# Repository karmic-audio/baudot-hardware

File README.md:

# baudot hardware

Based on the Monome Teletype.

Schematic/PCB diagram converted from Eagle to KiCAD.

Firmware: https://github.com/karmic-audio/baudot-software

## License

CC-BY-SA 3.0. Do not use the name "monome" or "teletype" in derivative works.

Created by brian crabtree (bcrabtree@monome.org)
Modified by Serge Bazanski (q3k@q3k.org) for Karmic Audio.

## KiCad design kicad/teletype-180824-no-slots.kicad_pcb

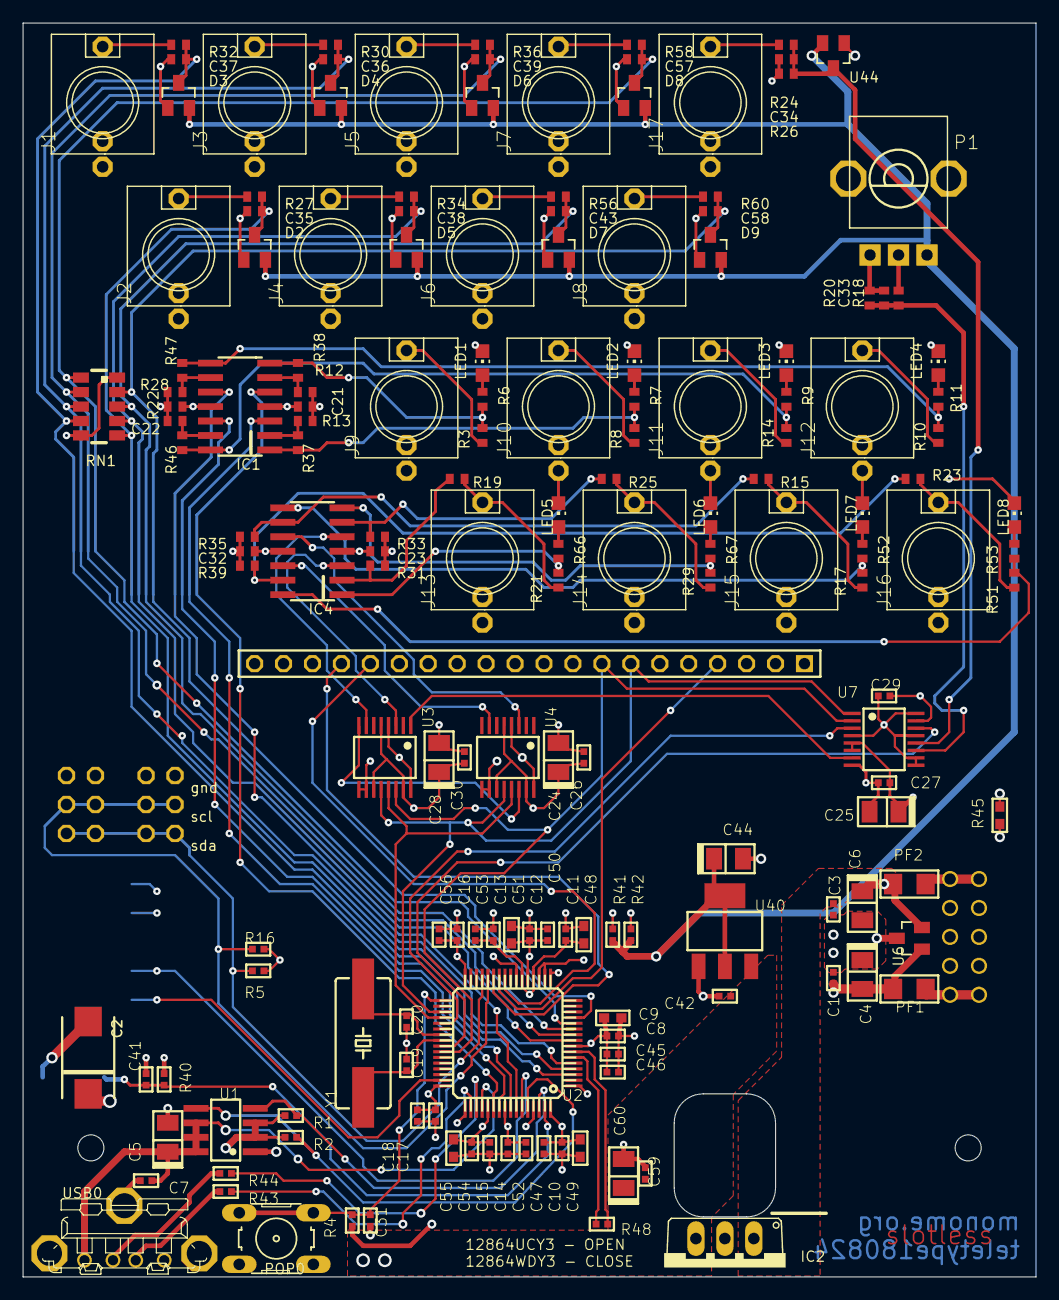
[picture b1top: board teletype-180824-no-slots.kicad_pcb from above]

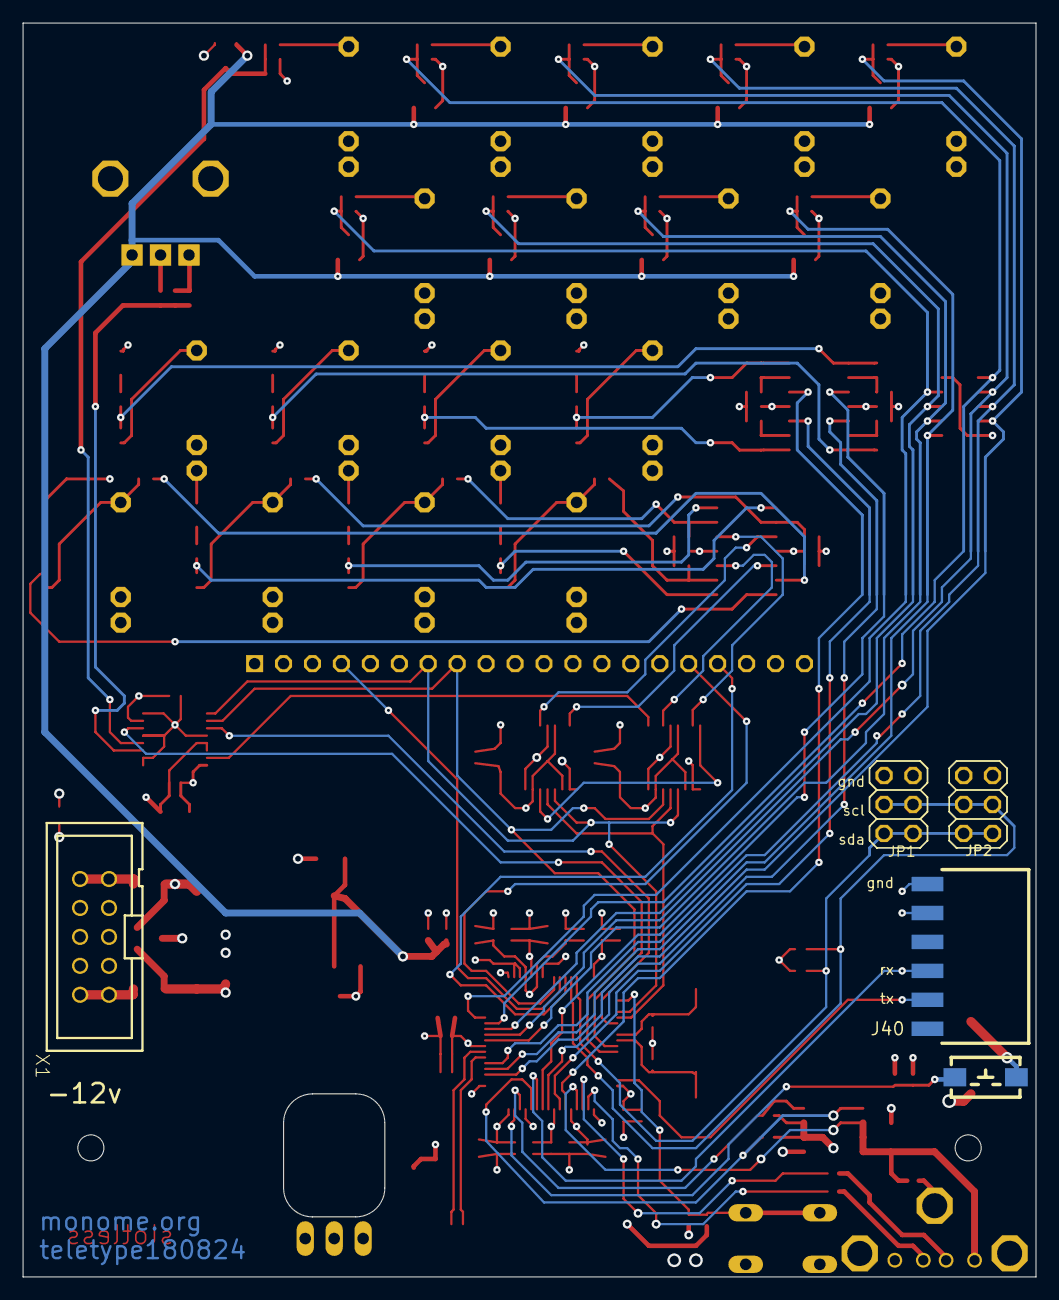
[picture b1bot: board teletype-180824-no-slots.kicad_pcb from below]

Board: 4 copper layers, 88.9 x 110.0 mm, 172 parts (5 on the bottom side), 98 nets.

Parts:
C1, C3, C7, C18, C21, C22, C23, C26, C27, C29, C30, C31, C32, C41, C42, C46, C47, C50, C56, C59: 100n; C0402
C2: 220u; C7343-43
C4, C6, C24, C25, C28, C44, C60: 10u; C1206_T
C5: 4.7u; C1206_T
C8, C13, C14, C15: 2.7n; C0402
C9, C48, C55: 2.2u; C0603
C10, C12, C16, C17, C33, C45, C52, C53, C54: 33n; C0402
C11: 470p; C0402
C19, C20: 22p; C0402
C34, C35, C36, C37, C38, C39, C43, C57, C58: 1n; C0402
C49, C51: 4.7u; C0603
D2, D3, D4, D5, D6, D7, D8, D9: BAS70-04; SOT23
IC1: TL074; SO14
IC2: OKI-78SR; TO220V
IC4: OPA4171; SO14
J1, J2, J3, J4, J5, J6, J7, J8, J9, J10, J11, J12, J13, J14, J15, J16, J17: WQP-PJ301M-12_JACK
J40: ISP-ROW
JP1, JP2: 2X03
JP5: OLED128X64; OLED-ALEPH
LED1, LED2, LED3, LED4: OR; CHIP-LED0805
LED5, LED6, LED7, LED8: W; CHIP-LED0805
P1: 10k; ALPS_POT_VERTICAL
PF1, PF2: PTC-F0805-15V; F1206
POP0: SWITCH-OMRON_B3F-10XX
R1, R2: 47k; R0402
R3, R8, R10, R14, R17, R21, R29, R51: 1k; R0402
R4, R6, R7, R9, R11, R12, R13, R18, R22, R26, R28, R31, R33, R35, R39, R40: 10k; R0402
R5, R16: 2k; R0402
R15, R19, R23, R24, R25, R27, R30, R32, R34, R36, R56, R58, R60: 30k; R0402
R20: 31k6; R0402
R37, R38, R46, R47, R52, R53, R66, R67: 20k; R0402
R41, R42, R48: 0; R0402
R43, R44: 39; R0402
R45: 0; R0603
RN1: 47k; MNR35
SW40: PANASONIC-EVQ
U1: TPS2021; SO08
U2: AT32UC3B064/0128/0256; TQFP64-10X10
U3, U4: AD5687R; TSSOP16
U6, U44: BAS70-04; SOT23
U7: AD7923; TSSOP16
U40: ADP3339; SOT223
USB0: SHAPES_PONY_MOLEX-USB-VERT; SHAPES_PONY_MOLEX-USB
X1: 2510-; PAK100_2500-10
Y1: 12mhz; HC49UP

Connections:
+3V3: C24.+, C25.+, C26.2, C27.2, C28.+, C29.2, C30.2, C44.+, D2.2, D3.2, D4.2, D5.2, D6.2, D7.2, D8.2, D9.2, JP5.2, P1.P$1, R4.2, R5.2, R16.2, R40.2, R41.2, R42.2, U2.18, U2.19, U3.5, U3.11, U3.15, U4.5, U4.11, U4.15, U7.5, U7.6, U7.15, U40.2, U40.4, U44.2
+5V: C2.+, C42.2, C59.2, C60.+, IC2.3, R1.2, R2.2, U1.2, U1.3, U40.3
+12V: C3.2, C6.+, C21.1, C23.1, IC1.4, IC2.1, IC4.4, PF2.2, U6.2
+IN: PF2.1, X1.9, X1.10
-12V: C1.2, C4.-, C22.2, C32.2, IC1.11, IC4.11, PF1.2, U6.1
-IN: PF1.1, X1.1, X1.2
A00: C37.1, D3.3, R32.2, RN1.7, U2.3
A01: C35.1, D2.3, R27.2, RN1.5, U2.4
A02: C36.1, D4.3, R30.2, RN1.8, U2.5
A03: C38.1, D5.3, R34.2, RN1.4, U2.9
A04: C39.1, D6.3, R36.2, RN1.9, U2.10
A05: C43.1, D7.3, R56.2, RN1.3, U2.11
A06: C57.1, D8.3, R58.2, RN1.10, U2.12
A07: C58.1, D9.3, R60.2, RN1.2, U2.13
AGND: C24.-, C25.-, C26.1, C27.1, C28.-, C29.1, C30.1, C33.2, C34.2, P1.P$3, R20.2, R26.1, R45.1, U3.4, U3.9, U3.10, U3.16, U4.4, U4.9, U4.10, U4.16, U7.4, U7.8, U7.9, U7.10, U7.13, U7.16, U44.1
B08: IC1.5, U2.54
B09: IC1.3, U2.55
B10: IC1.12, U2.57
B11: IC1.10, U2.58
CS0: U2.36, U3.13, U4.13
CS1: U2.37, U7.3
CS2: JP5.17, U2.27
CV-IN0: C34.1, R24.2, R26.2, U7.12, U44.3
CV-IN1: C33.1, R18.2, R20.1, U7.11
CV-OUT0: IC4.3, U3.3
CV-OUT1: IC4.5, U3.7
CV-OUT2: IC4.10, U4.3
CV-OUT3: IC4.12, U4.7
DM: R44.2, USB0.2
DP: R43.2, USB0.3
GND: C1.1, C2.-, C3.1, C4.+, C5.-, C6.-, C7.1, C8.1, C9.1, C10.1, C11.1, C12.1, C13.1, C14.1, C15.1, C16.1, C17.1, C18.1, C19.1, C20.1, C21.2, C22.1, C23.2, C31.2, C32.1, C35.2, C36.2, C37.2, C38.2, C39.2, C41.2, C42.1, C43.2, C44.-, C45.1, C46.1, C47.1, C48.1, C49.1, C50.1, C51.1, C52.1, C53.1, C54.1, C55.1, C56.1, C57.2, C58.2, C59.1, C60.-, D2.1, D3.1, D4.1, D5.1, D6.1, D7.1, D8.1, D9.1, IC2.2, J1.SLEEVE, J2.SLEEVE, J3.SLEEVE, J4.SLEEVE, J5.SLEEVE, J6.SLEEVE, J7.SLEEVE, J8.SLEEVE, J9.SLEEVE, J10.SLEEVE, J11.SLEEVE, J12.SLEEVE, J13.SLEEVE, J14.SLEEVE, J15.SLEEVE, J16.SLEEVE, J17.SLEEVE, J17.TS, J40.1, J40.2, JP1.5, JP1.6, JP2.5, JP2.6, JP5.1, JP5.5, JP5.6, JP5.9, JP5.10, JP5.11, JP5.12, JP5.13, JP5.14, JP5.19, JP5.20, LED1.C, LED2.C, LED3.C, LED4.C, LED5.C, LED6.C, LED7.C, LED8.C, POP0.3, POP0.4, R12.1, R13.1, R22.1, R28.1, R31.1, R33.1, R35.1, R39.1, R45.2, RN1.1, RN1.6, SW40.1, U1.1, U2.1, U2.17, U2.23, U2.49, U2.61, U6.3, U40.1, USB0.GND, USB0.M1, USB0.M2, USB0.M4, X1.3, X1.4, X1.5, X1.6, X1.7, X1.8
MISO: U2.41, U7.14
MOSI: JP5.8, U2.42, U3.14, U7.2
unnamed: R44.1, U2.51
unnamed: R43.1, U2.50
unnamed: IC1.7, R3.1, R6.1, R38.2
unnamed: U3.8, U4.14
unnamed: IC1.1, R7.1, R8.1, R37.2
unnamed: IC1.14, R9.1, R14.1, R46.2
unnamed: IC1.8, R10.1, R11.1, R47.2
unnamed: J9.TIP, R3.2
unnamed: J10.TIP, R8.2
unnamed: J11.TIP, R14.2
unnamed: J12.TIP, R10.2
unnamed: P1.P$2, R18.1
unnamed: IC4.1, R21.1, R66.1
unnamed: C20.2, U2.39, Y1.2
unnamed: IC4.7, R29.1, R67.1
unnamed: LED5.A, R66.2
unnamed: R48.1, U2.6
unnamed: R48.2, U2.7
unnamed: J15.TIP, R15.2, R17.2
unnamed: J16.TIP, R23.2, R51.2
unnamed: IC4.8, R17.1, R52.1
unnamed: LED6.A, R67.2
unnamed: IC4.14, R51.1, R53.1
unnamed: LED7.A, R52.2
unnamed: LED8.A, R53.2
unnamed: J13.TIP, R19.2, R21.2
unnamed: J17.TIP, R24.1
unnamed: J14.TIP, R25.2, R29.2
unnamed: J2.TIP, R27.1
unnamed: J3.TIP, R30.1
unnamed: J4.TIP, R34.1
unnamed: J1.TIP, R32.1
unnamed: J5.TIP, R36.1
unnamed: J6.TIP, R56.1
unnamed: J7.TIP, R58.1
unnamed: J8.TIP, R60.1
unnamed: LED1.A, R6.2
unnamed: LED2.A, R7.2
unnamed: LED3.A, R9.2
unnamed: LED4.A, R11.2
unnamed: C19.2, U2.40, Y1.1
NMI: C31.1, POP0.1, POP0.2, R4.1, U2.33
OLED-DC: JP5.4, U2.26
OLED-RES: JP5.16, U2.25
RESET: C41.1, R40.1, SW40.2, U2.63
RG1: IC1.6, R12.2, R38.1
RG2: IC1.2, R13.2, R37.1
RG3: IC1.13, R22.2, R46.1
RG4: IC1.9, R28.2, R47.1
RG5: IC4.2, R19.1, R31.2
RG6: IC4.6, R25.1, R33.2
RG7: IC4.9, R15.1, R35.2
RG8: IC4.13, R23.1, R39.2
RX: J40.4, U2.59
SCK: JP5.7, U2.35, U3.12, U4.12, U7.1
SCL: JP1.3, JP1.4, JP2.3, JP2.4, R16.1, U2.28
SDA: JP1.1, JP1.2, JP2.1, JP2.2, R5.1, U2.29
TX: J40.5, U2.47
USB-OC: R2.1, U1.5, U2.60
USB-VBOF: R1.1, U1.4, U2.62
VBUS: C5.+, C7.2, U1.6, U1.7, U1.8, U2.52, USB0.1
VDDIN: C12.2, C50.2, C51.2, R42.1, U2.21
VDDIO: C10.2, C16.2, C17.2, C18.2, C47.2, C49.2, C56.2, R41.1, U2.32, U2.48, U2.64
VDDOUT: C8.2, C9.2, C11.2, C13.2, C14.2, C15.2, C45.2, C46.2, C48.2, C52.2, C53.2, C54.2, C55.2, U2.8, U2.20, U2.22, U2.53, U2.56
VREF: U3.1, U7.7

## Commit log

2023-10-25 kicad: init from slotless
2023-10-25 mcad: init
2023-10-25 fab1: init
2023-10-25 README: prepare for release
2023-10-25 *: Cleanup leftovers from original repo
2023-10-25 mcad: remove leftover recover file
